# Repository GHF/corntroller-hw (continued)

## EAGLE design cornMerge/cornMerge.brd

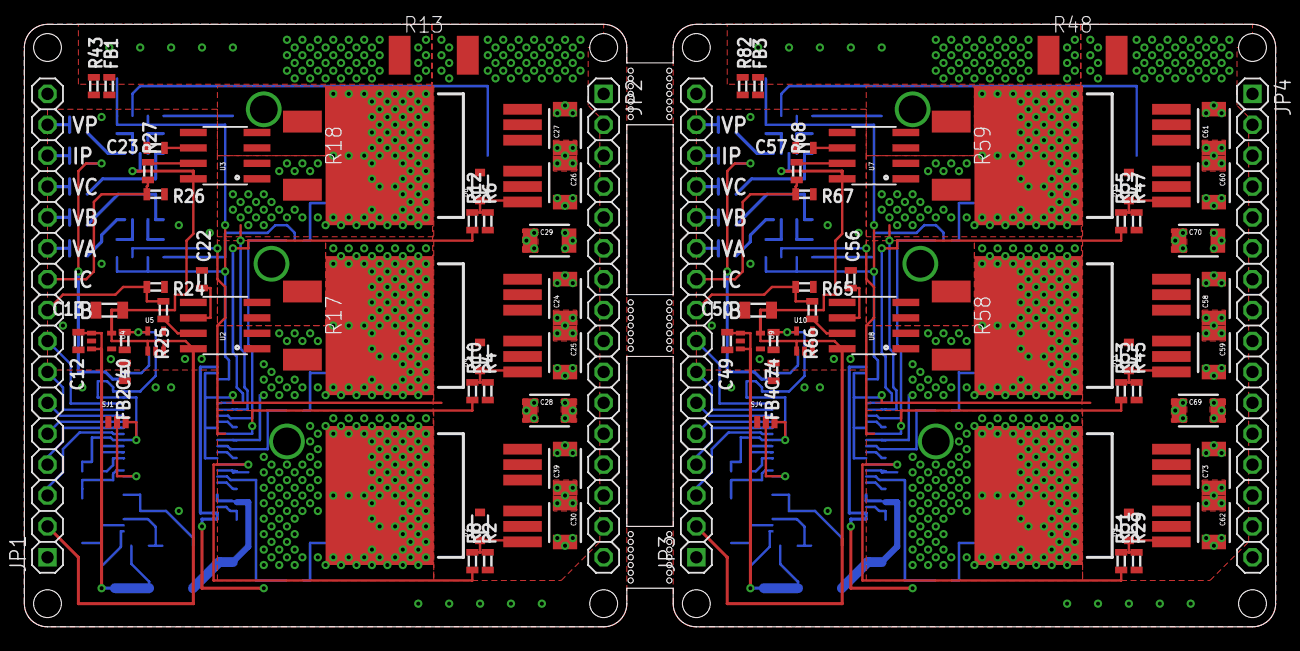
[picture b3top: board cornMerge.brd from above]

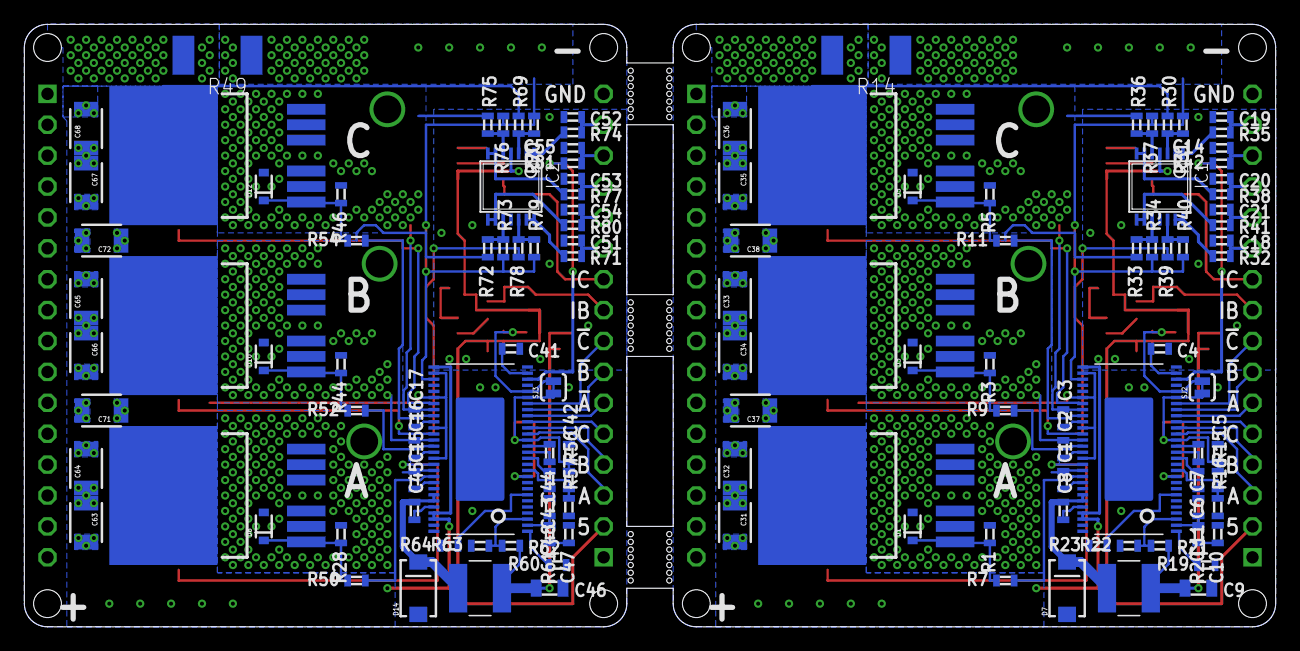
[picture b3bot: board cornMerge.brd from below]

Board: 2 copper layers, 102.9 x 49.5 mm, 208 parts (124 on the bottom side), 136 nets.

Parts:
C1, C2, C3, C8, C14, C15, C16, C17, C19, C22, C23, C45, C52, C55, C56, C57: 0.1uF; 0603
C4, C5, C12, C41, C42, C49: 1uF; 0603
C6, C43: 2.2uF; 0603
C7, C44: 0.022uF; 0603
C9, C13, C46, C50: 22uF; 0805
C10, C47: 6800pF; 0603
C11, C48: 120pF; 0603
C18, C20, C21, C51, C53, C54: 10000pF; 0603
C24, C25, C26, C27, C28, C29, C30, C31, C32, C33, C34, C35, C36, C37, C38, C39, C58, C59, C60, C61, C62, C63, C64, C65, C66, C67, C68, C69, C70, C71, C72, C73: 10uF; 1210
C40, C74: 10uF; 0603
D1, D2, D3, D4, D5, D6, D8, D9, D10, D11, D12, D13: ZENER; SOD-323
D7, D14: SMA-DIODE
FB1, FB2, FB3, FB4: 0603
IC1, IC2: OPA4743EA; TSSOP14
JP1, JP2, JP3, JP4: 1X16-S
L1, L2: 22uH; TAIYO-YUDEN_NR50
R1, R2, R3, R4, R5, R6, R23, R28, R29, R42, R44, R45, R46, R47, R64, R81: 22k; 0603
R7, R8, R9, R10, R11, R12, R50, R51, R52, R53, R54, R55: 0R; 0603
R13, R14, R17, R18, R48, R49, R58, R59: 1mR; R2512
R15, R56: 91k; 0603
R16, R57: 12k; 0603
R19, R60: 205k; 0603
R20, R61: 16.2k; 0603
R21, R62: 59k; 0603
R22, R63: 10k; 0603
R24, R26, R31, R34, R37, R40, R65, R67, R70, R73, R76, R79: 330R; 0603
R25, R27, R66, R68: 1K; 0603
R30, R32, R33, R35, R36, R38, R39, R41, R69, R71, R72, R74, R75, R77, R78, R80: 6.8K; 0603
R43, R82: 0603
SJ1, SJ4: SJ_X
SJ2, SJ3: SJ_2S-TRACE
S_AH, S_AH1: D2PAK-7
S_AL, S_AL1: D2PAK-7
S_BH, S_BH1: D2PAK-7
S_BL, S_BL1: D2PAK-7
S_CH, S_CH1: D2PAK-7
S_CL, S_CL1: D2PAK-7
U1, U6: DRV8302; HTSSOP-56
U2, U3, U7, U8: ACS712; SO08
U4, U5, U9, U10: V_REG_LDOSMD2; SC70

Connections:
!PWM_A: JP1.4, U1.18
!PWM_A1: JP3.4, U6.18
!PWM_B: JP1.6, U1.20
!PWM_B1: JP3.6, U6.20
!PWM_C: JP1.8, U1.22
!PWM_C1: JP3.8, U6.22
+3V1: C74.1, SJ3.2, U6.24, U10.5
+3V3: C40.1, SJ2.2, U1.24, U5.5
+5V: C13.1, IC1.4, JP1.2, U2.8, U3.8, U4.5, U5.1, U5.3
+5V1: C50.1, IC2.4, JP3.2, U7.8, U8.8, U9.5, U10.1, U10.3
AGND: C4.2, C12.2, C13.2, C14.2, C18.1, C19.1, C20.1, C21.1, C22.2, C23.2, C40.2, FB2.1, IC1.11, R24.2, R26.2, U1.28, U2.5, U3.5, U4.2, U5.2
AGND1: C41.2, C49.2, C50.2, C51.1, C52.1, C53.1, C54.1, C55.2, C56.2, C57.2, C74.2, FB4.1, IC2.11, R65.2, R67.2, U6.28, U7.5, U8.5, U9.2, U10.2
GND: C5.2, C6.2, C9.2, C10.1, C11.1, D7.A, FB1.1, FB2.2, JP1.1, JP1.16, JP2.1, JP2.16, R16.1, R19.1, R22.2, R23.2, R43.1, SJ1.1, U1.8, U1.9, U1.12, U1.PWRPAD
GND2: C42.2, C43.2, C46.2, C47.1, C48.1, D14.A, FB3.1, FB4.2, JP3.1, JP3.16, JP4.1, JP4.16, R57.1, R60.1, R63.2, R64.2, R82.1, SJ4.1, U6.8, U6.9, U6.12, U6.PWRPAD
I_A: JP1.9, R24.1, R25.1
I_A1: JP3.9, R65.1, R66.1
I_B: JP1.10, R26.1, R27.1
I_B1: JP3.10, R67.1, R68.1
I_B_5V: R25.2, U2.7
I_B_5V1: R66.2, U8.7
I_C_5V: R27.2, U3.7
I_C_5V1: R68.2, U7.7
I_P: C14.1, JP1.14, R42.1
I_P1: C55.1, JP3.14, R81.1
M_A: C1.2, D1.2, R1.1, R39.2, S_AH.2, S_AH.3, S_AH.5, S_AH.6, S_AH.7, S_AL.4, U1.46
M_A1: C15.2, D8.2, R28.1, R78.2, S_AH1.2, S_AH1.3, S_AH1.5, S_AH1.6, S_AH1.7, S_AL1.4, U6.46
M_B: R17.1, U2.3, U2.4
M_B1: R58.1, U8.3, U8.4
M_C: R18.1, U3.3, U3.4
M_C1: R59.1, U7.3, U7.4
unnamed: R7.1, U1.47
unnamed: R8.1, U1.45
unnamed: R42.2, U1.26
unnamed: D1.1, R1.2, R7.2, S_AH.1
unnamed: D3.1, R3.2, R9.2, S_BH.1
unnamed: C22.1, U2.6
unnamed: D4.1, R4.2, R10.2, S_BL.1
unnamed: R21.1, R22.1, U1.3
unnamed: D5.1, R5.2, R11.2, S_CH.1
unnamed: C23.1, U3.6
unnamed: D6.1, R6.2, R12.2, S_CL.1
unnamed: R9.1, U1.42
unnamed: C1.1, U1.48
unnamed: C2.1, U1.43
unnamed: C3.1, U1.38
unnamed: R10.1, U1.40
unnamed: R11.1, U1.37
unnamed: D2.1, R2.2, R8.2, S_AL.1
unnamed: R12.1, U1.35
unnamed: SJ1.2, U1.10
unnamed: C5.1, R15.2, SJ1.3, SJ2.1, U1.16, U1.23
unnamed: C4.1, U1.27
unnamed: C6.1, U1.13
unnamed: C7.2, U1.14
unnamed: C7.1, U1.15
unnamed: R15.1, R16.2, U1.11
unnamed: D8.1, R28.2, R50.2, S_AH1.1
unnamed: D10.1, R44.2, R52.2, S_BH1.1
unnamed: C8.2, D7.C, L1.P$2, U1.50, U1.51
unnamed: C8.1, U1.52
unnamed: C11.2, R20.1, U1.2
unnamed: C10.2, R20.2
unnamed: R19.2, U1.1
unnamed: R23.1, U1.7
unnamed: D11.1, R45.2, R53.2, S_BL1.1
unnamed: IC1.1, IC1.2, R35.1
unnamed: D12.1, R46.2, R54.2, S_CH1.1
unnamed: D13.1, R47.2, R55.2, S_CL1.1
unnamed: C15.1, U6.48
unnamed: C16.1, U6.43
unnamed: IC1.6, IC1.7, R38.1
unnamed: IC1.8, IC1.9, R41.1
unnamed: IC1.13, IC1.14, R32.1
unnamed: IC1.3, R30.1, R31.2
unnamed: C17.1, U6.38
unnamed: IC1.10, R33.1, R34.2
unnamed: IC1.5, R36.1, R37.2
unnamed: IC1.12, R39.1, R40.2
unnamed: D9.1, R29.2, R51.2, S_AL1.1
unnamed: R50.1, U6.47
unnamed: R51.1, U6.45
unnamed: R52.1, U6.42
unnamed: R53.1, U6.40
unnamed: R54.1, U6.37
unnamed: R55.1, U6.35
unnamed: SJ4.2, U6.10
unnamed: C42.1, R56.2, SJ3.1, SJ4.3, U6.16, U6.23
unnamed: C41.1, U6.27
unnamed: C43.1, U6.13
unnamed: C44.2, U6.14
unnamed: C44.1, U6.15
unnamed: R56.1, R57.2, U6.11
unnamed: C45.2, D14.C, L2.P$2, U6.50, U6.51
unnamed: C45.1, U6.52
unnamed: C48.2, R61.1, U6.2
unnamed: C47.2, R61.2
unnamed: R60.2, U6.1
unnamed: R62.1, R63.1, U6.3
unnamed: R64.1, U6.7
unnamed: IC2.1, IC2.2, R74.1
unnamed: IC2.6, IC2.7, R77.1
unnamed: IC2.8, IC2.9, R80.1
unnamed: IC2.13, IC2.14, R71.1
unnamed: IC2.3, R69.1, R70.2
unnamed: IC2.10, R72.1, R73.2
unnamed: IC2.5, R75.1, R76.2
unnamed: IC2.12, R78.1, R79.2
unnamed: R81.2, U6.26
unnamed: C56.1, U8.6
unnamed: C57.1, U7.6
PWM_A: JP1.3, U1.17
PWM_A1: JP3.3, U6.17
PWM_B: JP1.5, U1.19
PWM_B1: JP3.5, U6.19
PWM_C: JP1.7, U1.21
PWM_C1: JP3.7, U6.21
R_B: C2.2, D3.2, R3.1, R17.2, R33.2, S_BH.2, S_BH.3, S_BH.5, S_BH.6, S_BH.7, S_BL.4, U1.41, U2.1, U2.2
R_B1: C16.2, D10.2, R44.1, R58.2, R72.2, S_BH1.2, S_BH1.3, S_BH1.5, S_BH1.6, S_BH1.7, S_BL1.4, U6.41, U8.1, U8.2
R_C: C3.2, D5.2, R5.1, R18.2, R36.2, S_CH.2, S_CH.3, S_CH.5, S_CH.6, S_CH.7, S_CL.4, U1.36, U3.1, U3.2
R_C1: C17.2, D12.2, R46.1, R59.2, R75.2, S_CH1.2, S_CH1.3, S_CH1.5, S_CH1.6, S_CH1.7, S_CL1.4, U6.36, U7.1, U7.2
V+: C24.1, C25.1, C26.1, C27.1, C28.1, C29.1, C30.1, C31.1, C32.1, C33.1, C34.1, C35.1, C36.1, C37.1, C38.1, C39.1, R30.2, S_AH.4, S_BH.4, S_CH.4, U1.29, U1.53, U1.54
V+1: C58.1, C59.1, C60.1, C61.1, C62.1, C63.1, C64.1, C65.1, C66.1, C67.1, C68.1, C69.1, C70.1, C71.1, C72.1, C73.1, R69.2, S_AH1.4, S_BH1.4, S_CH1.4, U6.29, U6.53, U6.54
V-: FB1.2, R13.1, R14.1, R31.1, R34.1, R37.1, R40.1, R43.2, U1.31
V-1: FB3.2, R48.1, R49.1, R70.1, R73.1, R76.1, R79.1, R82.2, U6.31
VCC: C9.1, C12.1, L1.P$1, R21.2, U4.1, U4.3
VCC1: C46.1, C49.1, L2.P$1, R62.2, U9.1, U9.3
V_A: C18.2, JP1.11, R32.2
V_A1: C51.2, JP3.11, R71.2
V_B: C21.2, JP1.12, R41.2
V_B1: C54.2, JP3.12, R80.2
V_C: C20.2, JP1.13, R38.2
V_C1: C53.2, JP3.13, R77.2
V_LOW: C24.2, C25.2, C26.2, C27.2, C28.2, C29.2, C30.2, C31.2, C32.2, C33.2, C34.2, C35.2, C36.2, C37.2, C38.2, C39.2, D2.2, D4.2, D6.2, R2.1, R4.1, R6.1, R13.2, R14.2, S_AL.2, S_AL.3, S_AL.5, S_AL.6, S_AL.7, S_BL.2, S_BL.3, S_BL.5, S_BL.6, S_BL.7, S_CL.2, S_CL.3, S_CL.5, S_CL.6, S_CL.7, U1.30, U1.34, U1.39, U1.44
V_LOW1: C58.2, C59.2, C60.2, C61.2, C62.2, C63.2, C64.2, C65.2, C66.2, C67.2, C68.2, C69.2, C70.2, C71.2, C72.2, C73.2, D9.2, D11.2, D13.2, R29.1, R45.1, R47.1, R48.2, R49.2, S_AL1.2, S_AL1.3, S_AL1.5, S_AL1.6, S_AL1.7, S_BL1.2, S_BL1.3, S_BL1.5, S_BL1.6, S_BL1.7, S_CL1.2, S_CL1.3, S_CL1.5, S_CL1.6, S_CL1.7, U6.30, U6.34, U6.39, U6.44
V_P: C19.2, JP1.15, R35.2
V_P1: C52.2, JP3.15, R74.2

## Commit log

2012-03-20 Initial checkin
2012-03-21 Update TODO
2012-03-27 Iterated TinyHusk to v2.1
2012-04-02 New merged TinyHusk submitted for fab on 3/26
2012-04-09 Change values of I_B & I_C resistor dividers
2012-04-16 Iterate to v2.2; just fix silkscreen labels for PWM inputs
